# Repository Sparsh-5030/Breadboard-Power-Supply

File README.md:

This is a fun project of creating a pcb design in KiCad 5 for a breadboard power supply.

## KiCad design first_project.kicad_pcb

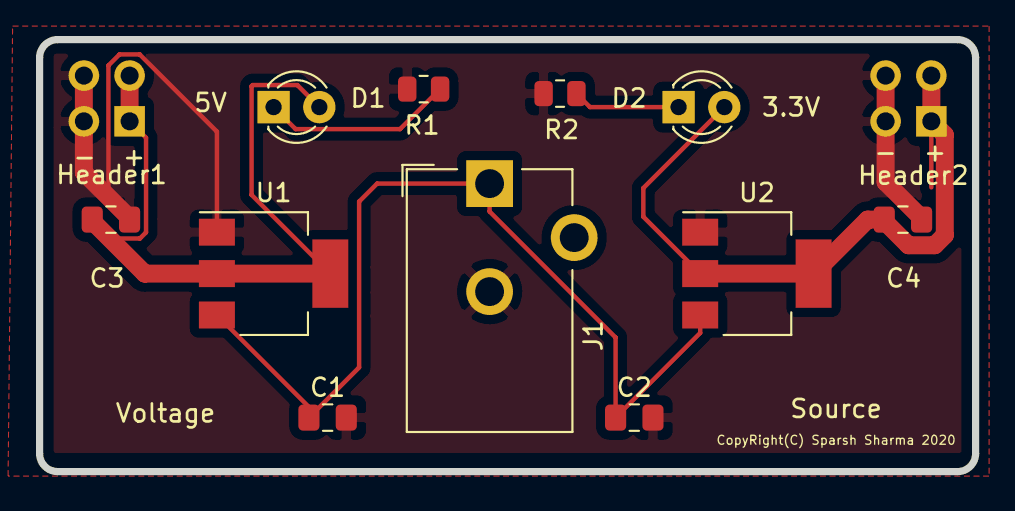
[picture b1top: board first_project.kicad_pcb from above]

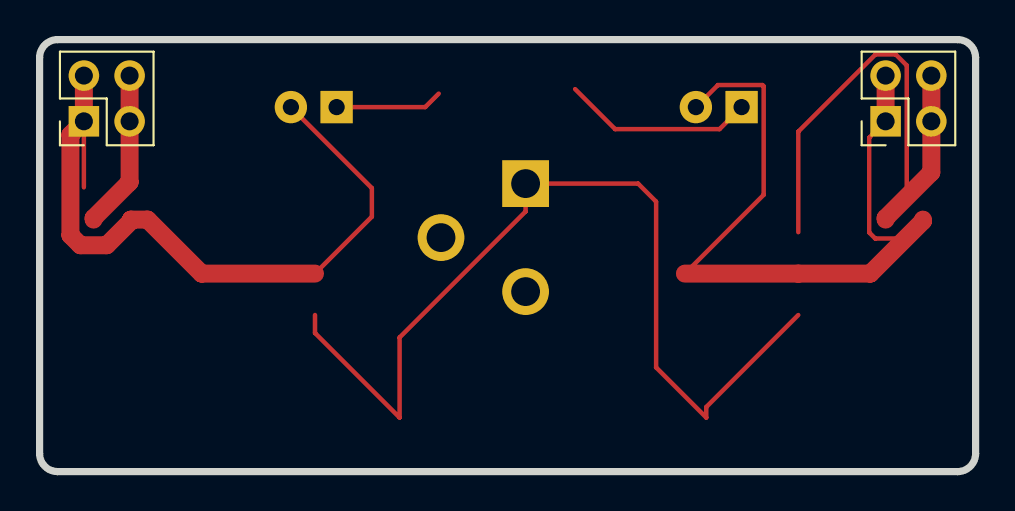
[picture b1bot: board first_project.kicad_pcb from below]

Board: 2 copper layers, 52.0 x 24.0 mm, 13 parts (2 on the bottom side), 6 nets.

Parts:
C1, C2: 10uF; C_0805_2012Metric_Pad1.18x1.45mm_HandSolder
C3, C4: 22uF; C_0805_2012Metric_Pad1.18x1.45mm_HandSolder
D1, D2: LED; LED_D3.0mm
Header1, Header2: Conn_02x02_Odd_Even; PinHeader_2x02_P2.54mm_Vertical
J1: Barrel_Jack; BarrelJack_CUI_PJ-102AH_Horizontal
R1, R2: 1K; R_0805_2012Metric
U1: 5V; SOT-223-3_TabPin2
U2: 3.3V; SOT-223-3_TabPin2

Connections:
GND: C1.2, C2.2, C3.2, C4.2, Header1.3, Header1.4, Header2.3, Header2.4, J1.2, R1.1, R2.1, U1.1, U2.1
unnamed: C1.1, C2.1, J1.1, U1.3, U2.3
unnamed: C3.1, D1.2, Header1.1, Header1.2, U1.2
unnamed: C4.1, D2.2, Header2.1, Header2.2, U2.2
unnamed: D1.1, R1.2
unnamed: D2.1, R2.2

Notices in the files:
first_project.kicad_pcb:
CopyRight(C) Sparsh Sharma 2020
